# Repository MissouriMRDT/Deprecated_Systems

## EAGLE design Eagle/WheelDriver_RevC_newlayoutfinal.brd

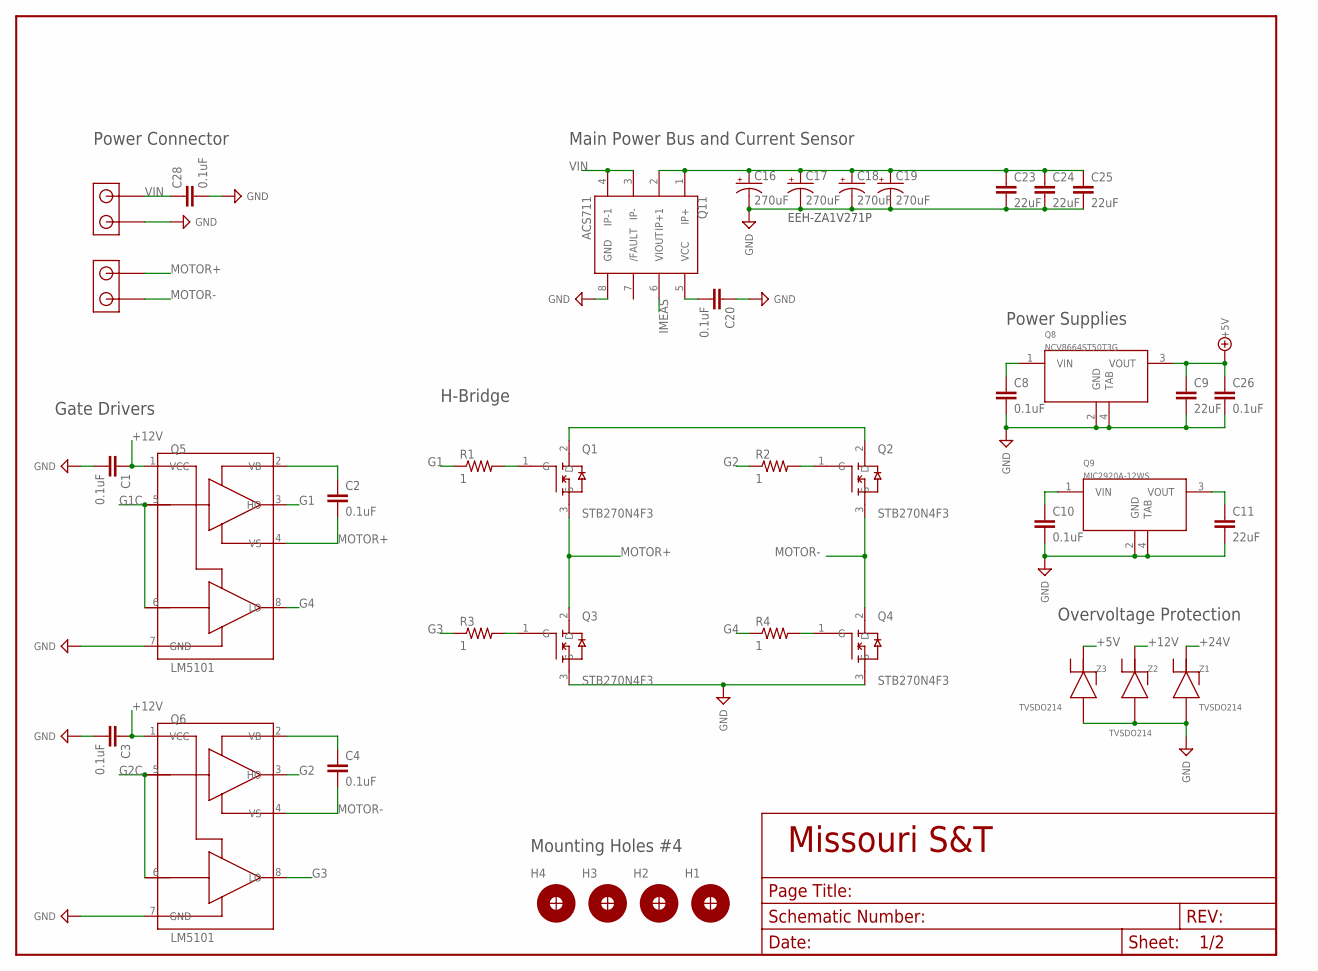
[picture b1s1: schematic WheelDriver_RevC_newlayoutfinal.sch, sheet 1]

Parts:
C1: 0.1uF; C_0805
C2, C3, C4, C8, C10, C20, C26, C28: 0.1uF; C_1206
C9, C11, C23, C24, C25: 22uF; C_1206
C16, C17, C18, C19: 270uF; C_10MMSM
H1, H2, H3, H4: H_MNTHOLE_#4
J4, J5: J_1546074-2; THERM_BLOCK_2
Q1, Q2, Q3, Q4: STB270N4F3; TO-263
Q5, Q6: LM5101; SOIC8
Q8: NCV8664ST50T3G; SOT-223
Q9: MIC2920A-12WS; SOT-223
Q11: ACS711; SOIC8
R1, R2: 1; R_0805
R3, R4: 1; R_1206
Z1, Z2, Z3: TVSDO214; DO-214AC

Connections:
+5V: C9.1, C26.1, Q8.3 (VOUT), Z3.C; also elsewhere on the board
+12V: C1.1, C3.1, C11.1, Q5.1 (VCC), Q6.1 (VCC), Q9.3 (VOUT), Z2.C
+24V: C10.1, C16.+, C17.+, C18.+, C19.+, C23.1, C24.1, C25.1, Q1.2 (D), Q2.2 (D), Q9.1 (VIN), Q11.1 (IP+), Q11.2 (IP+1), Z1.C; also elsewhere on the board
G1: Q5.3 (HO), R1.1
G1C: Q5.5 (HI), Q5.6 (LI); also elsewhere on the board
G2: Q6.3 (HO), R2.1
G2C: Q6.5 (HI), Q6.6 (LI); also elsewhere on the board
G3: Q6.8 (LO), R3.1
G4: Q5.8 (LO), R4.1
GND: C1.2, C3.2, C8.2, C9.2, C10.2, C11.2, C16.-, C17.-, C18.-, C19.-, C20.1, C23.2, C24.2, C25.2, C26.2, C28.2, J4.P$1, Q3.3 (S), Q4.3 (S), Q5.7 (GND), Q6.7 (GND), Q8.2 (GND), Q8.4 (TAB), Q9.2 (GND), Q9.4 (TAB), Q11.8 (GND), Z1.A, Z2.A, Z3.A; also elsewhere on the board
IMEAS: Q11.6 (VIOUT); also elsewhere on the board
MOTOR+: C2.2, J5.P$2, Q1.3 (S), Q3.2 (D), Q5.4 (VS)
MOTOR-: C4.2, J5.P$1, Q2.3 (S), Q4.2 (D), Q6.4 (VS)
unnamed: Q1.1 (G), R1.2
unnamed: Q3.1 (G), R3.2
unnamed: Q2.1 (G), R2.2
unnamed: Q4.1 (G), R4.2
unnamed: C2.1, Q5.2 (VB)
unnamed: C4.1, Q6.2 (VB)
unnamed: C20.2, Q11.5 (VCC)
VIN: C8.1, C28.1, J4.P$2, Q8.1 (VIN), Q11.3 (IP-), Q11.4 (IP-1)

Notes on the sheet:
EEH-ZA1V271P
Power Connector
Gate Drivers
H-Bridge
Overvoltage Protection
Mounting Holes #4
Power Supplies
Main Power Bus and Current Sensor

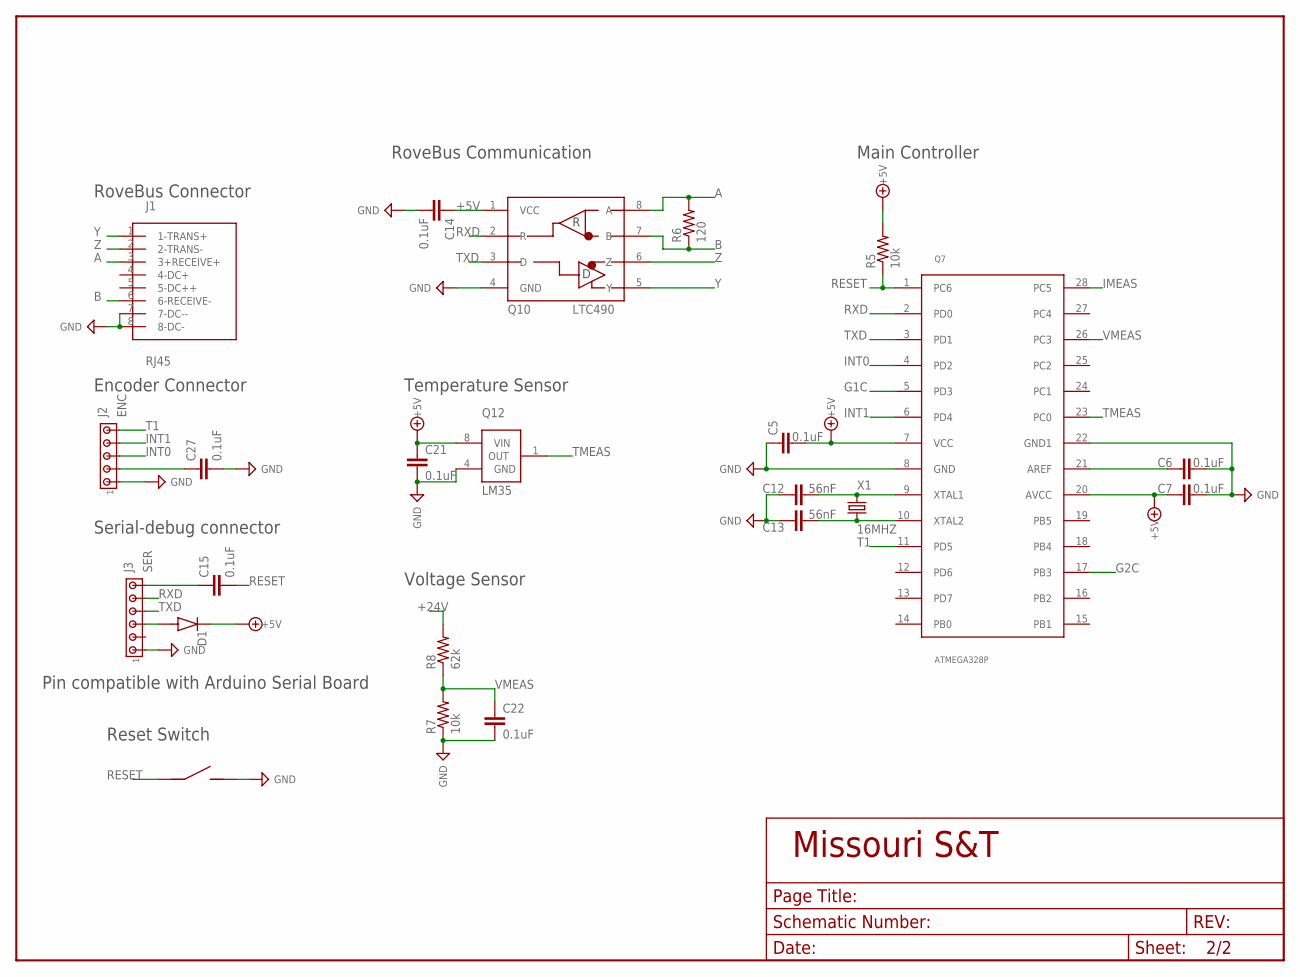
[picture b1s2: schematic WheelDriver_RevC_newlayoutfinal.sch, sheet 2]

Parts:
C5, C14, C27: 0.1uF; C_1206
C6, C7, C15, C21, C22: 0.1uF; C_0805
C12, C13: 56nF; C_1206
D1: D_DIODEDO214AC; DO-214AC
J1: RJ45; RJ45-CAT5E
J2: ENC; J_MTA100_5P
J3: SER; J_MTA100_6P
J6: J_MC32857; J_TOGGLE
Q7: ATMEGA328P; DIP28
Q10: LTC490; SOIC8
Q12: LM35; SOIC8
R5, R7: 10k; R_0805
R6: 120; R_0805
R8: 62k; R_0805
X1: 16MHZ; HC-49

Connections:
+5V: C5.2, C7.1, C14.1, C21.1, C27.1, D1.C, J2.2, Q7.7 (VCC), Q7.20 (AVCC), Q10.1 (VCC), Q12.8 (VIN), R5.2; also elsewhere on the board
+24V: R8.2; also elsewhere on the board
A: J1.3 (3+RECEIVE+), Q10.8 (A), R6.2
B: J1.6 (6-RECEIVE-), Q10.7 (B), R6.1
EXTRESET: C15.1, J3.6
G1C: Q7.5 (PD3); also elsewhere on the board
G2C: Q7.17 (PB3); also elsewhere on the board
GND: C5.1, C6.2, C7.2, C12.1, C13.1, C14.2, C21.2, C22.2, C27.2, J1.7 (7-DC--), J1.8 (8-DC-), J2.1, J3.1, J6.P$2 (2), Q7.8 (GND), Q7.22 (GND1), Q10.4 (GND), Q12.4 (GND), R7.1; also elsewhere on the board
IMEAS: Q7.28 (PC5); also elsewhere on the board
INT0: J2.3, Q7.4 (PD2)
INT1: J2.4, Q7.6 (PD4)
unnamed: C12.2, Q7.9 (XTAL1), X1.P$1 (1)
unnamed: C6.1, Q7.21 (AREF)
unnamed: D1.A, J3.3
unnamed: C13.2, Q7.10 (XTAL2), X1.P$2 (2)
RESET: C15.2, J6.P$1 (1), Q7.1 (PC6), R5.1
RXD: J3.5, Q7.2 (PD0), Q10.2 (R)
T1: J2.5, Q7.11 (PD5)
TMEAS: Q7.23 (PC0), Q12.1 (OUT)
TXD: J3.4, Q7.3 (PD1), Q10.3 (D)
VMEAS: C22.1, Q7.26 (PC3), R7.2, R8.1
Y: J1.1 (1-TRANS+), Q10.5 (Y)
Z: J1.2 (2-TRANS-), Q10.6 (Z)

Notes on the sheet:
RoveBus Connector
Encoder Connector
Serial-debug connector
Pin compatible with Arduino Serial Board
Reset Switch
RoveBus Communication
Temperature Sensor
Voltage Sensor
Main Controller

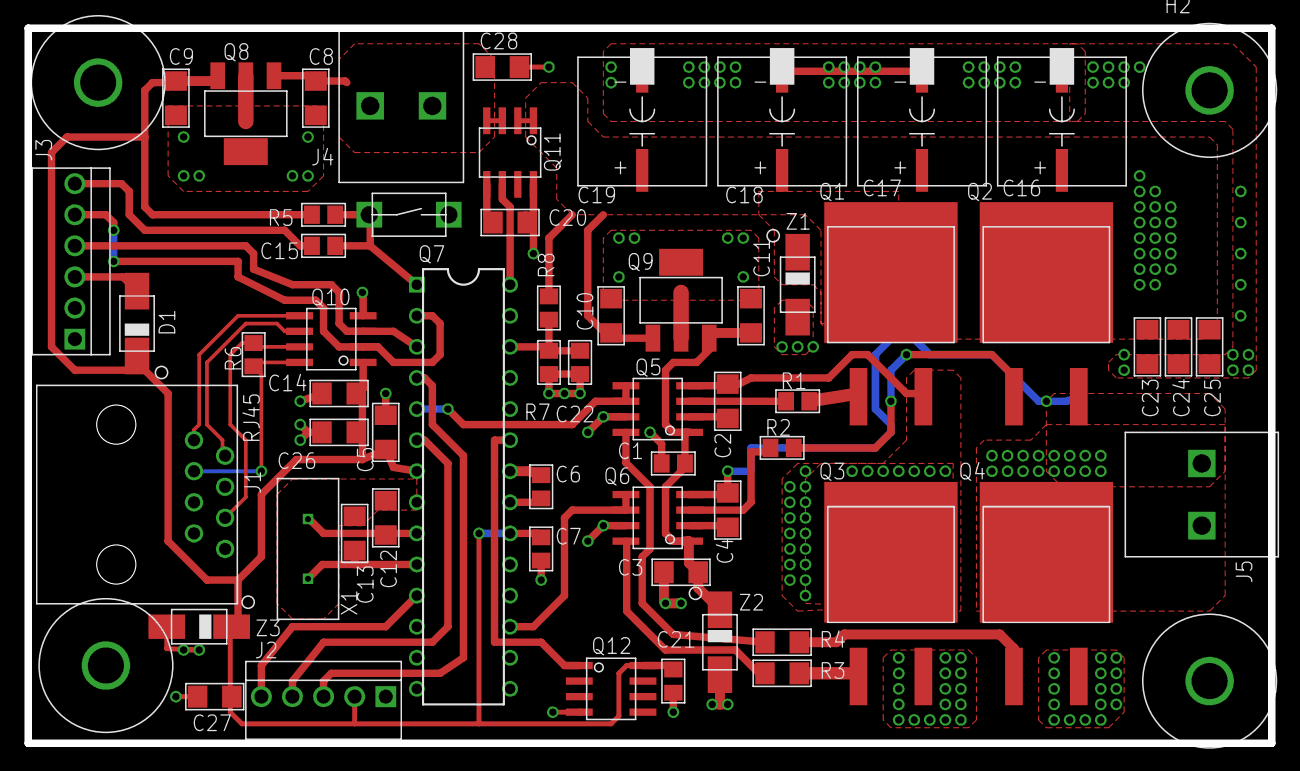
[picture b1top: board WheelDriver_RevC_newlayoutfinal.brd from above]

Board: 2 copper layers, 101.6 x 58.4 mm, 63 parts (0 on the bottom side), 38 nets.

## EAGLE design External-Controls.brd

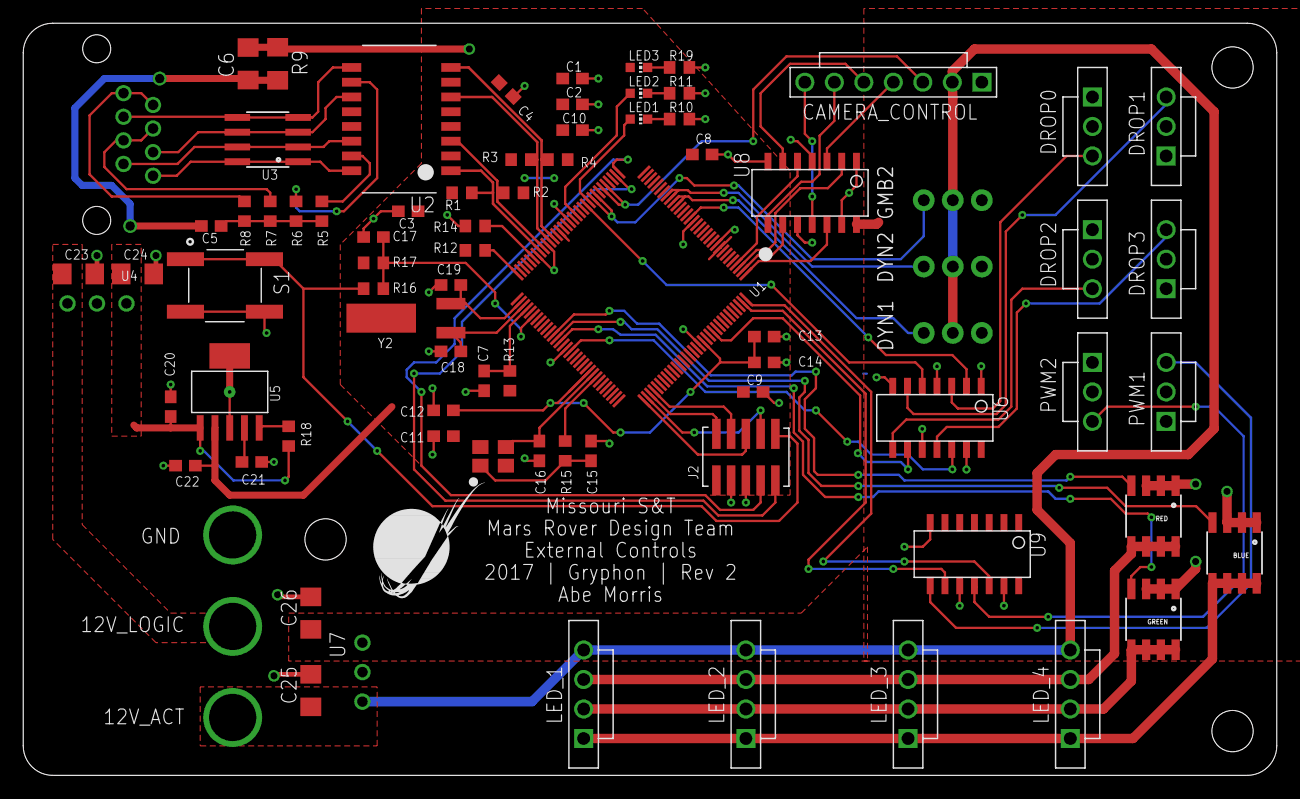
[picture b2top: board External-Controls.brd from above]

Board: 2 copper layers, 108.0 x 64.8 mm, 85 parts (0 on the bottom side), 74 nets.

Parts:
BLUE: IRF7821TRPBF; SOIC8
C1, C2, C3, C4, C7, C8, C9, C10, C11, C12, C17, C20, C21: 0.1uF; C0603
C5: 1000pF; C0603
C6: 4700pF; C1206
C13: 1.0uF; C0603
C14, C22: 2.2uF; C0603
C15, C16, C18, C19: 12pF; C0603
C23, C24, C25, C26: 10uF; C1206
CAMERA_CONTROL: SL07; MOLEX-70543-0006
DROP0, DROP1, DROP2, DROP3: SERVOMOLEX_SL_VERT_TH; MOLEX-70543-0002
DYN1, DYN2: DYNAMIXEL-1X03VERT; MLX-SPOX5267-3PIN
GMB2: DYNAMIXEL-1X03VERT; MLX-SPOX5267-3PIN
GREEN: IRF7821TRPBF; SOIC8
J1: RJ45KEYSTONE-942; KEYSTONE-942
J2: JTAG_ARM_10PIN; CON_2X5_50MIL
J3: APP_2POS_CONFIG12V_HORIZ; APP45_12V_HORIZ_CONFIG
J8: APPPP45_PCB_HORIZ_RIGHT; APP45_PCB_HORIZ_RIGHT
LED1, LED2: GREEN; CHIP-LED0603
LED3: ORANGE; CHIP-LED0603
LED_1, LED_2, LED_3, LED_4: SL04VERT; MOLEX-70543-0003
PWM1, PWM2: SERVOMOLEX_SL_VERT_TH; MOLEX-70543-0002
R1, R3, R4: 49.9; R0603
R2: 49.4; R0603
R5, R6, R7, R8: 75; R0603
R9: 1M; R1206
R10, R11, R19: 330; R0603
R12: 1M; R0603
R13: 51; R0603
R14: 4.87k 1%; R0603
R15: 2k; R0603
R16: 100; R0603
R17: 10k; R0603
R18: 100k; R0603
RED: IRF7821TRPBF; SOIC8
S1: SWITCH_TACTILE; SWITCH_6MM_6MM_TE_CON_SMD
U1: TM4C1294NCPDT; TQFP-128
U2: HX1198FNL
U3: SLVU2.8-4; SOIC8
U4, U7: OKI-78SR-5/1.5-W36HC; OKI-78SR_HORIZ
U5: TPS73733DCQ; SOT-223-6
U6, U8, U9: SN74AHCT125; SOIC14
U$1: MRDT_LOGO
U$2, U$3, U$4: MOUNTING_HOLE#6; #6_SCREW
Y1: NX3225GA; NDK3.2X2.5
Y2: CRYATL_32K_SMD; CRYSTAL_32K_SMD

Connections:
!RESET: J2.P10, R16.2, S1.P$3, S1.P$4
+3V3: C1.1, C2.1, C3.1, C4.1, C8.1, C9.1, C10.1, C11.1, C22.1, J2.P1, LED3.A, R1.1, R2.1, R3.1, R4.1, R12.2, R13.2, R17.1, U1.P$7, U1.P$8, U1.P$9, U1.P$16, U1.P$26, U1.P$28, U1.P$39, U1.P$47, U1.P$51, U1.P$52, U1.P$69, U1.P$79, U1.P$90, U1.P$101, U1.P$113, U1.P$122, U2.P$2, U2.P$7, U5.2
+5V_ACT: C26.1, DROP0.2, DROP1.2, DROP2.2, DROP3.2, PWM1.2, PWM2.2, U6.14, U7.3, U8.14, U9.1, U9.4, U9.14
+5V_LOGIC: C20.1, C24.1, R18.1, U4.3, U5.1
+12V_ACT: C25.1, CAMERA_CONTROL.2, DYN1.VCC, DYN2.VCC, GMB2.VCC, J8.P$1, LED_1.4, LED_2.4, LED_3.4, LED_4.4, U7.1
+12V_LOGIC: C23.1, J3.12V, U4.1
BLUE: BLUE.5, BLUE.6, BLUE.7, BLUE.8, LED_1.1, LED_2.1, LED_3.1, LED_4.1
BLUE_SIG: BLUE.4, U1.P$77
CAM_PWM_0: CAMERA_CONTROL.4, U8.3
CAM_PWM_1: CAMERA_CONTROL.5, U8.6
CAM_PWM_2: CAMERA_CONTROL.6, U8.8
CAM_PWM_3: CAMERA_CONTROL.7, U8.11
CTRL_0: U1.P$3, U8.2
CTRL_1: U1.P$4, U8.5
CTRL_2: U1.P$2, U8.9
CTRL_3: U1.P$1, U8.12
DROPBAY_0: U1.P$18, U6.2
DROPBAY_1: U1.P$43, U6.5
DROPBAY_2: U1.P$118, U6.9
DROPBAY_3: U1.P$81, U6.12
DYN_1: CAMERA_CONTROL.3, U1.P$37, U1.P$38
DYN_2: GMB2.DATA, U1.P$40, U1.P$41
DYN_3: DYN1.DATA, U1.P$22, U1.P$23
DYN_4: DYN2.DATA, U1.P$24, U1.P$25
EN0LED0: LED1.A, U1.P$42
EN0LED1: LED2.A, U1.P$46
EN0RXI_N: R4.2, U1.P$53, U2.P$8
EN0RXI_P: R3.2, U1.P$54, U2.P$6
EN0TXO_N: R2.2, U1.P$56, U2.P$3
EN0TXO_P: R1.2, U1.P$57, U2.P$1
GND: BLUE.1, BLUE.2, BLUE.3, C1.2, C2.2, C3.2, C4.2, C6.2, C7.2, C8.2, C9.2, C10.2, C11.2, C12.2, C13.2, C14.2, C15.2, C16.2, C17.2, C18.2, C19.2, C20.2, C21.2, C22.2, C23.2, C24.2, C25.2, C26.2, CAMERA_CONTROL.1, DROP0.1, DROP1.1, DROP2.1, DROP3.1, DYN1.GND, DYN2.GND, GMB2.GND, GREEN.1, GREEN.2, GREEN.3, J2.P3, J2.P5, J3.GND, PWM1.1, PWM2.1, R9.1, R10.2, R11.2, R14.1, R19.2, RED.1, RED.2, RED.3, S1.P$1, S1.P$2, U1.P$10, U1.P$17, U1.P$48, U1.P$55, U1.P$58, U1.P$80, U1.P$114, U4.2, U5.3, U5.6, U6.1, U6.4, U6.7, U6.10, U6.13, U7.2, U8.1, U8.4, U8.7, U8.10, U8.13, U9.7, U9.10, U9.13
GREEN: GREEN.5, GREEN.6, GREEN.7, GREEN.8, LED_1.2, LED_2.2, LED_3.2, LED_4.2
GREEN_SIG: GREEN.4, U1.P$78
N_$1: R5.2, U2.P$15
N_$3: R6.2, U2.P$10
N_$4: J1.P$7, U2.P$14, U3.2, U3.7
N_$5: J1.P$6, U2.P$11, U3.3, U3.6
N_$6: J1.P$8, U2.P$16, U3.1, U3.8
N_$7: J1.P$3, U2.P$9, U3.4, U3.5
N_$8: LED2.C, R11.1
N_$9: LED1.C, R10.1
N_$10: C7.1, R13.1, U1.P$68
N_$11: J1.P$4, J1.P$5, R7.2
N_$12: R12.1, U1.P$64
N_$13: J1.P$1, J1.P$2, R8.2
N_$14: C5.1, R5.1, R6.1, R7.1, R8.1
N_$15: C5.2, C6.1, R9.2
N_$16: C12.1, C13.1, C14.1, U1.P$87, U1.P$115
N_$17: R15.2, U1.P$89
N_$18: C16.1, U1.P$88, Y1.P$3
N_$19: R14.2, U1.P$59
N_$20: C17.1, R16.1, R17.2, U1.P$70
N_$21: C15.1, R15.1, Y1.P$1
N_$22: C18.1, U1.P$67, Y2.P$2
N_$23: C19.1, U1.P$66, Y2.P$1
N_$25: R18.2, U5.5
N_$26: LED3.C, R19.1
N_$27: C21.1, U5.4
PWM1: U1.P$128, U9.12
PWM2: U1.P$127, U9.9
RED: LED_1.3, LED_2.3, LED_3.3, LED_4.3, RED.5, RED.6, RED.7, RED.8
RED_SIG: RED.4, U1.P$76
RX: J2.P7, U1.P$33
SERVO_0: DROP0.3, U6.3
SERVO_1: DROP1.3, U6.6
SERVO_2: DROP2.3, U6.8
SERVO_3: DROP3.3, U6.11
SERVO_4: PWM2.3, U9.11
SERVO_5: PWM1.3, U9.8
TARGET_TCK/SWCLK: J2.P4, U1.P$100
TARGET_TDI: J2.P8, U1.P$98
TARGET_TDO/SWO: J2.P6, U1.P$97
TARGET_TMS/SWDIO: J2.P2, U1.P$99
TX: J2.P9, U1.P$34

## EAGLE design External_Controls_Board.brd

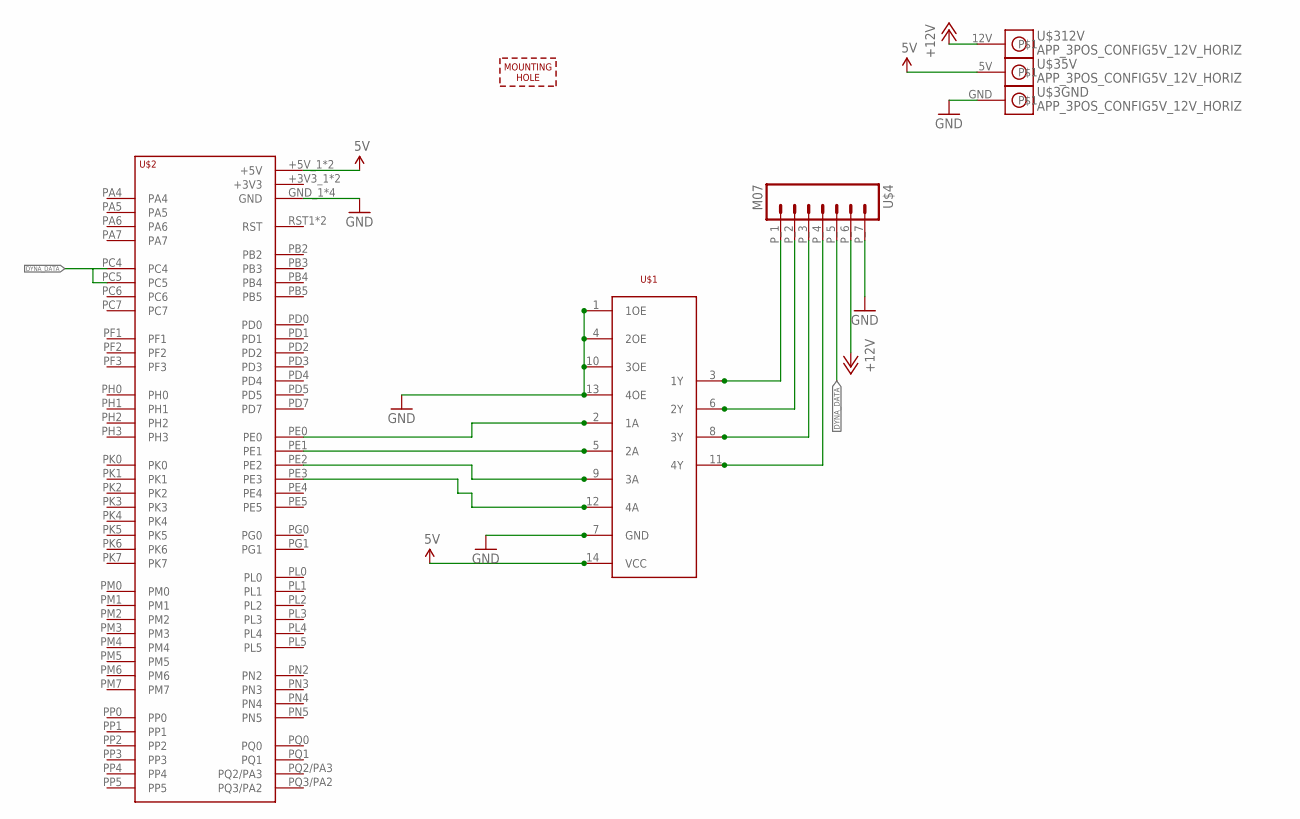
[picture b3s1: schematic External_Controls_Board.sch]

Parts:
U$1: SN74AHCT125; SOIC14
U$2: TIVA-C-CONNECTED
U$3: APP_3POS_CONFIG5V_12V_HORIZ; APP45_5V_12V_HORIZ_CONFIG
U$4: M07; MOLEX_43650-07
U$6: MOUNTING_HOLE#8; #8_SCREW

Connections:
+5V: U$1.14 (VCC), U$2.+5V_1 (+5V), U$2.+5V_2 (+5V), U$3.5V
+12V: U$3.12V, U$4.P_6 (6)
DYNA_DATA: U$2.PC4, U$2.PC5, U$4.P_5 (5)
GND: U$1.1 (1OE), U$1.4 (2OE), U$1.7 (GND), U$1.10 (3OE), U$1.13 (4OE), U$2.GND_1 (GND), U$2.GND_2 (GND), U$2.GND_3 (GND), U$2.GND_4 (GND), U$3.GND, U$4.P_7 (7)
PWM0_3.3: U$1.12 (4A), U$2.PE3
PWM0_5: U$1.11 (4Y), U$4.P_4 (4)
PWM1_3.3: U$1.9 (3A), U$2.PE2
PWM1_5: U$1.8 (3Y), U$4.P_3 (3)
PWM2_3.3: U$1.5 (2A), U$2.PE1
PWM2_5: U$1.6 (2Y), U$4.P_2 (2)
PWM3_3.3: U$1.2 (1A), U$2.PE0
PWM3_5: U$1.3 (1Y), U$4.P_1 (1)

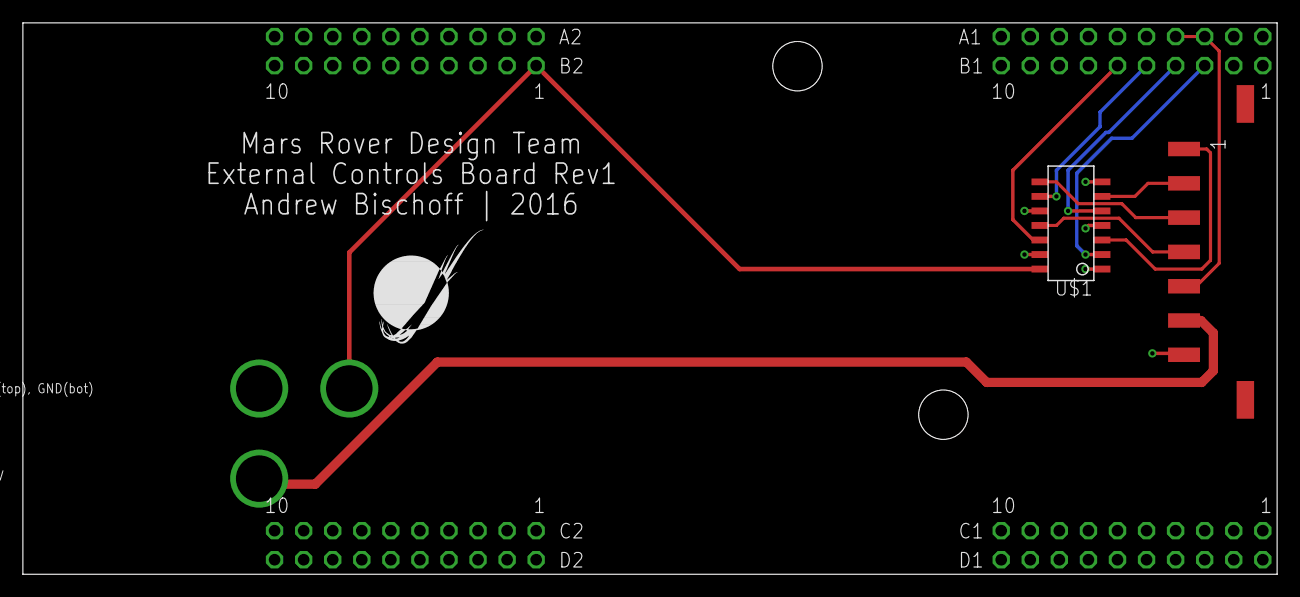
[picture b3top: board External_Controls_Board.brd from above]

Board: 2 copper layers, 109.6 x 48.2 mm, 7 parts (0 on the bottom side), 12 nets.

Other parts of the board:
U$5: MOUNTING_HOLE#8; #8_SCREW
U$7: MRDT_LOGO

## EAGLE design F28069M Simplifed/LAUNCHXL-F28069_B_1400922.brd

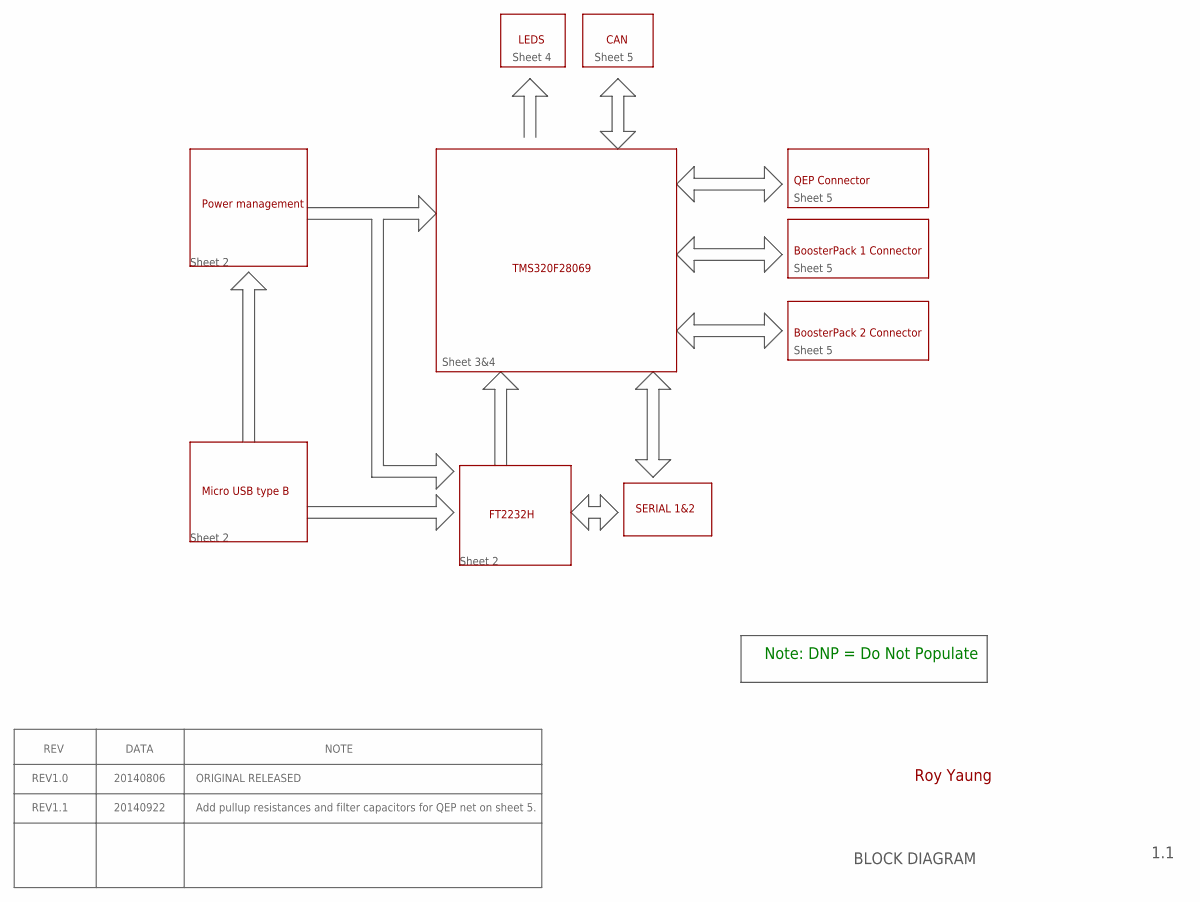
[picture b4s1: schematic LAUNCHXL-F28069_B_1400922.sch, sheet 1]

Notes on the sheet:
1.1
BLOCK DIAGRAM
Power management
Micro USB type B
FT2232H
TMS320F28069
BoosterPack 1 Connector
LEDS
CAN
SERIAL 1&2
Sheet 2
Sheet 3&4
BoosterPack 2 Connector
QEP Connector
Note: DNP = Do Not Populate
Roy Yaung
Sheet 5
Sheet 4
REV
DATA
NOTE
REV1.0
REV1.1
20140806
20140922
ORIGINAL RELEASED
Add pullup resistances and filter capacitors for QEP net on sheet 5.

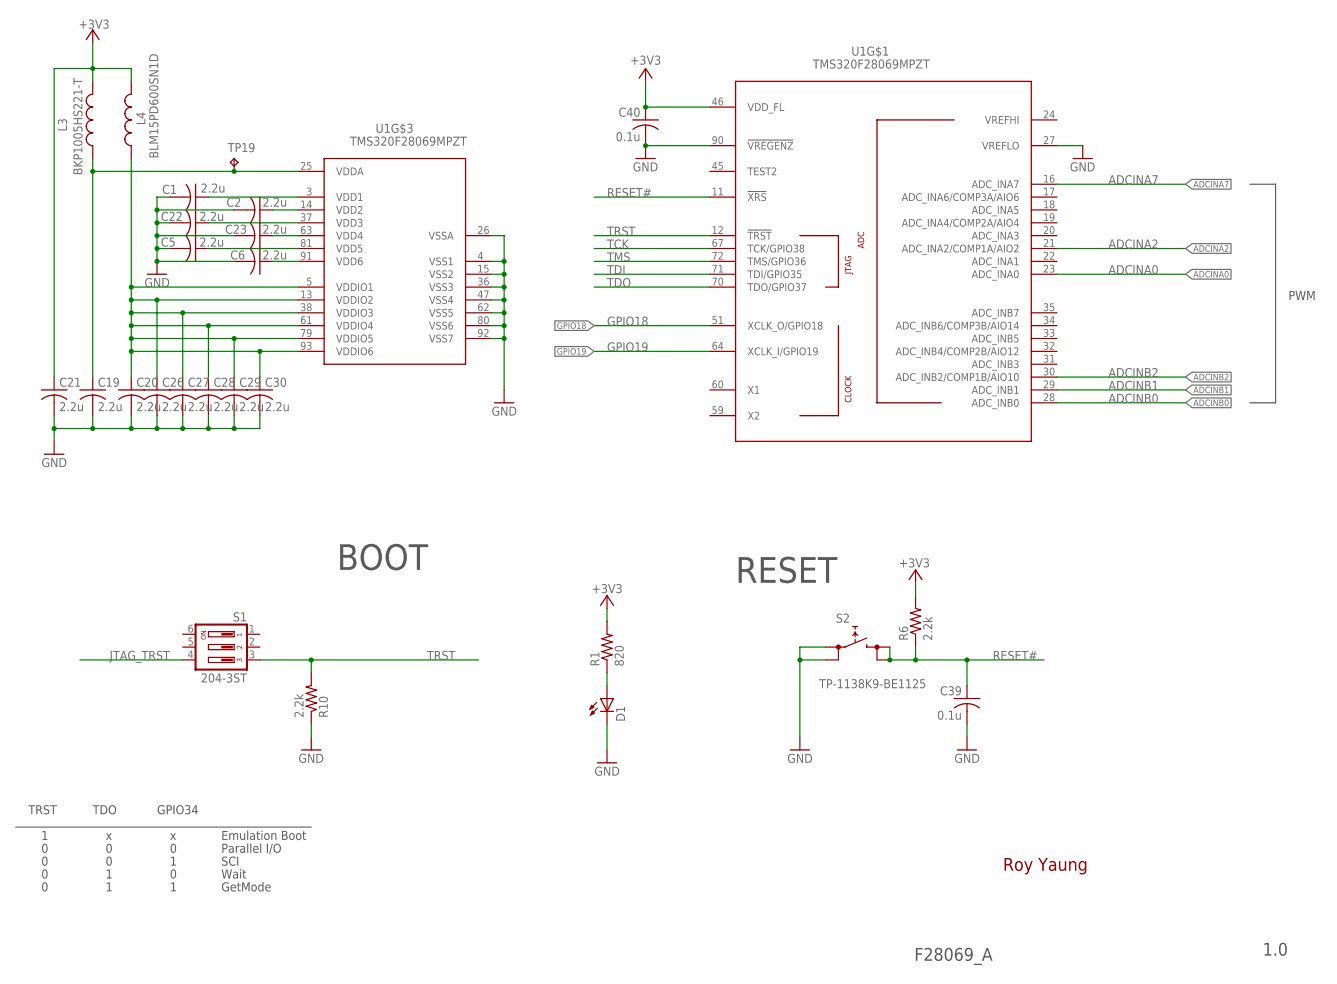
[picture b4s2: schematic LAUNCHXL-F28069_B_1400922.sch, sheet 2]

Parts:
C1, C2, C5, C6, C19, C20, C21, C22, C23, C26, C27, C28, C29, C30: 2.2u; C0402
C39, C40: 0.1u; C0402
D1: LEDCHIP-LED0603; CHIP-LED0603
L3: BKP1005HS221-T; R0402
L4: BLM15PD600SN1D; R0402
R1: 820; R0402
R6, R10: 2.2k; R0402
S1: 204-3ST; CTS-219-03
S2: TP-1138K9-BE1125; FSMJSMA
TP19: TESTPAD_TPB1,27; TESTPAD_B1,27
U1: TMS320F28069MPZT; PQFP100

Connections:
+3V3: C21.1, C40.1, L3.2, L4.2, R1.2, R6.2, U1.46 (VDD_FL); also elsewhere on the board
ADCINA0: U1.23 (ADC_INA0); also elsewhere on the board
ADCINA2: U1.21 (ADC_INA2/COMP1A/AIO2); also elsewhere on the board
ADCINA7: U1.16 (ADC_INA7); also elsewhere on the board
ADCINB0: U1.28 (ADC_INB0); also elsewhere on the board
ADCINB1: U1.29 (ADC_INB1); also elsewhere on the board
ADCINB2: U1.30 (ADC_INB2/COMP1B/AIO10); also elsewhere on the board
GND: C1.2, C2.2, C5.2, C6.2, C19.2, C20.2, C21.2, C22.2, C23.2, C26.2, C27.2, C28.2, C29.2, C30.2, C39.2, C40.2, D1.C, R10.1, S2.P$1 (0), S2.P$2 (0), U1.4 (VSS1), U1.15 (VSS2), U1.26 (VSSA), U1.27 (VREFLO), U1.36 (VSS3), U1.47 (VSS4), U1.62 (VSS5), U1.80 (VSS6), U1.90 (!VREGENZ), U1.92 (VSS7); also elsewhere on the board
GPIO18: U1.51 (XCLK_O/GPIO18); also elsewhere on the board
GPIO19: U1.64 (XCLK_I/GPIO19); also elsewhere on the board
JTAG_TRST: S1.4; also elsewhere on the board
unnamed: D1.A, R1.1
unnamed: C1.1, U1.3 (VDD1)
unnamed: C2.1, U1.14 (VDD2)
unnamed: C22.1, U1.37 (VDD3)
unnamed: C23.1, U1.63 (VDD4)
unnamed: C5.1, U1.81 (VDD5)
unnamed: C6.1, U1.91 (VDD6)
RESET#: C39.1, R6.1, S2.P$3 (1), S2.P$4 (1), U1.11 (!XRS); also elsewhere on the board
TCK: U1.67 (TCK/GPIO38); also elsewhere on the board
TDI: U1.71 (TDI/GPIO35); also elsewhere on the board
TDO: U1.70 (TDO/GPIO37); also elsewhere on the board
TMS: U1.72 (TMS/GPIO36); also elsewhere on the board
TRST: R10.2, S1.3, U1.12 (!TRST)
VDDA: C19.1, L3.1, TP19.TP, U1.25 (VDDA)
VDDIO: C20.1, C26.1, C27.1, C28.1, C29.1, C30.1, L4.1, U1.5 (VDDIO1), U1.13 (VDDIO2), U1.38 (VDDIO3), U1.61 (VDDIO4), U1.79 (VDDIO5), U1.93 (VDDIO6)

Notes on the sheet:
1.0
F28069_A
PWM
TDO
GPIO34
TRST
Emulation Boot
Parallel I/O
SCI
Wait
GetMode
RESET
BOOT
Roy Yaung

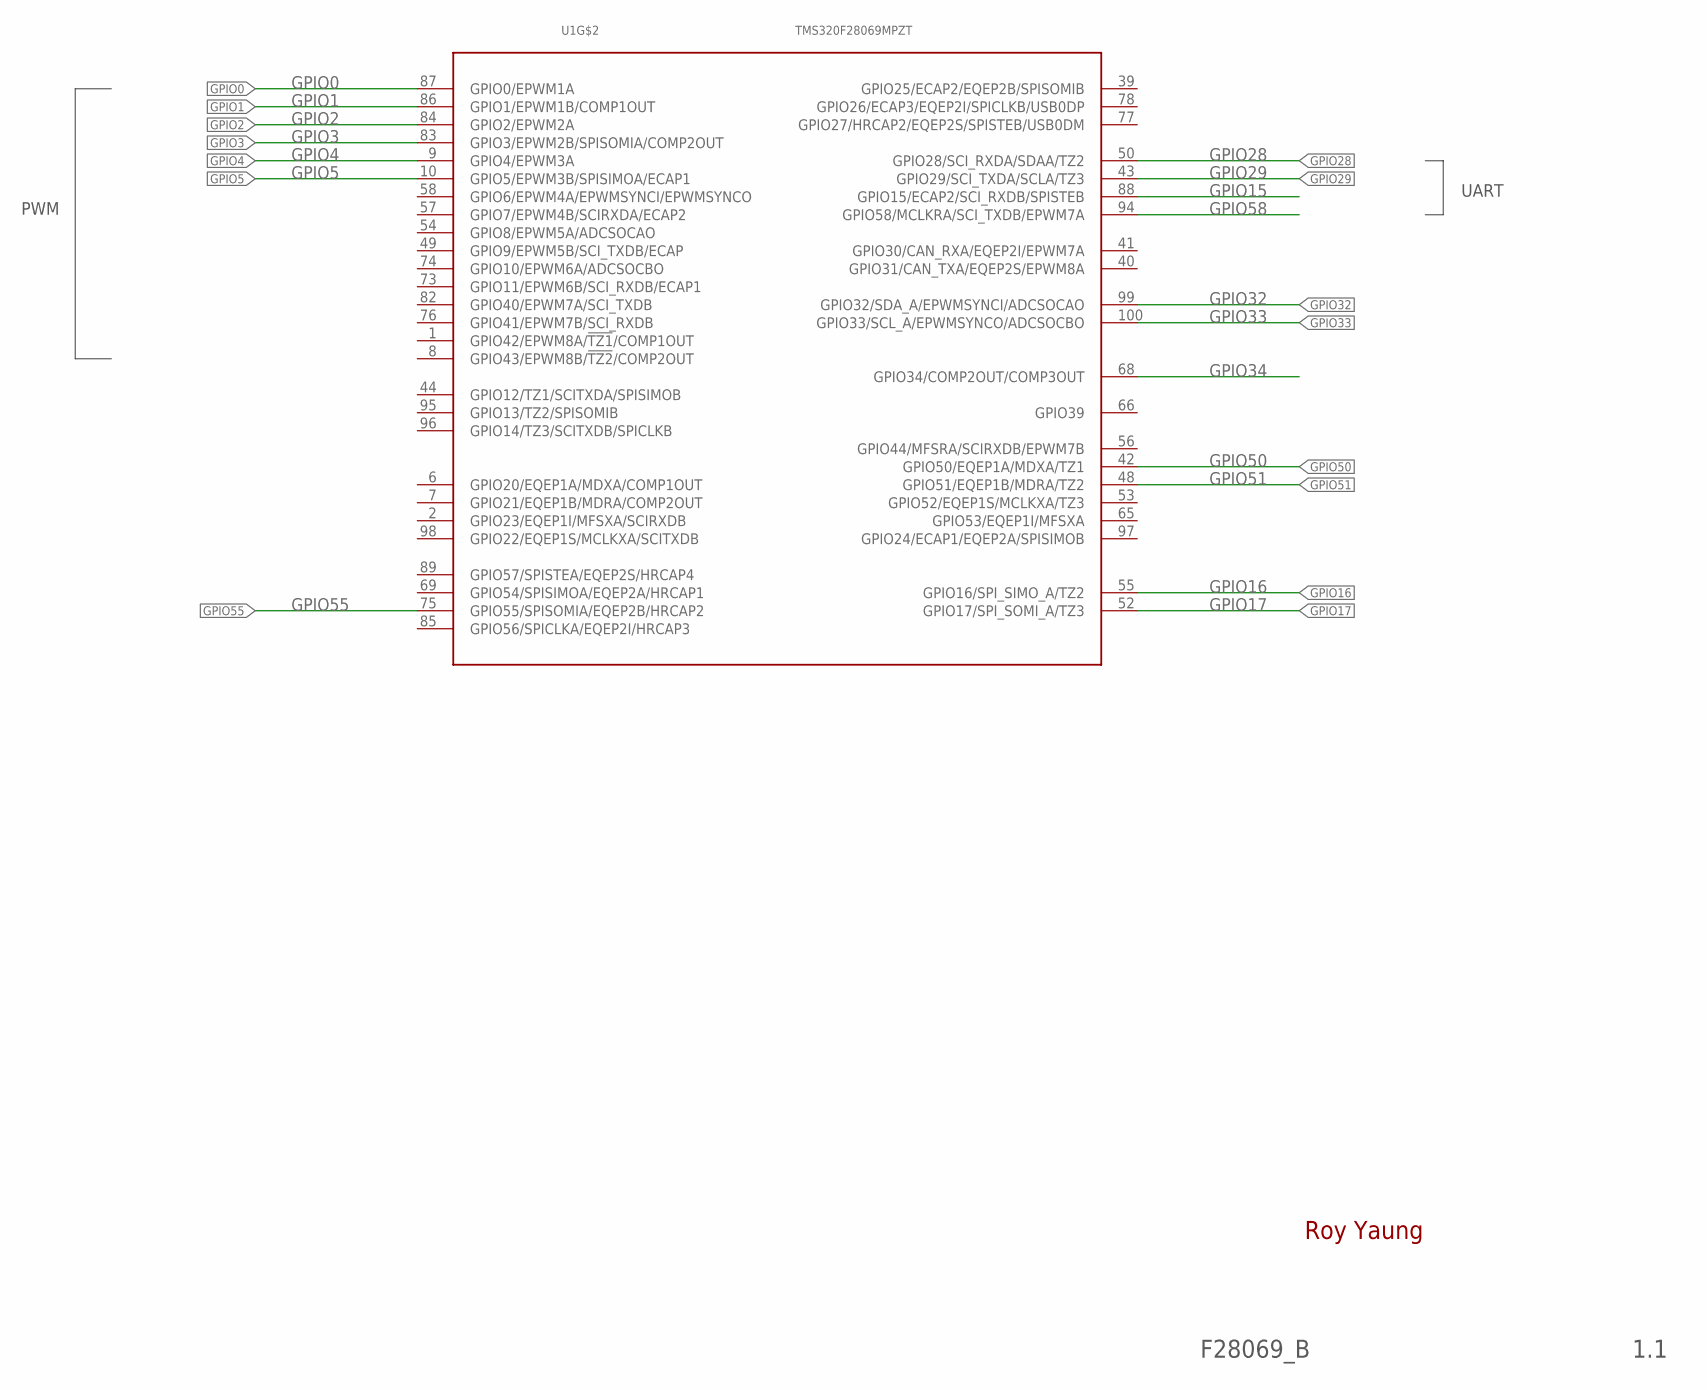
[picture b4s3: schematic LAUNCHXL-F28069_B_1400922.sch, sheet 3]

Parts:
U1: TMS320F28069MPZT; PQFP100

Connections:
GPIO0: U1.87 (GPIO0/EPWM1A); also elsewhere on the board
GPIO1: U1.86 (GPIO1/EPWM1B/COMP1OUT); also elsewhere on the board
GPIO2: U1.84 (GPIO2/EPWM2A); also elsewhere on the board
GPIO3: U1.83 (GPIO3/EPWM2B/SPISOMIA/COMP2OUT); also elsewhere on the board
GPIO4: U1.9 (GPIO4/EPWM3A); also elsewhere on the board
GPIO5: U1.10 (GPIO5/EPWM3B/SPISIMOA/ECAP1); also elsewhere on the board
GPIO15: U1.88 (GPIO15/ECAP2/SCI_RXDB/SPISTEB)
GPIO16: U1.55 (GPIO16/SPI_SIMO_A/TZ2); also elsewhere on the board
GPIO17: U1.52 (GPIO17/SPI_SOMI_A/TZ3); also elsewhere on the board
GPIO28: U1.50 (GPIO28/SCI_RXDA/SDAA/TZ2)
GPIO29: U1.43 (GPIO29/SCI_TXDA/SCLA/TZ3)
GPIO32: U1.99 (GPIO32/SDA_A/EPWMSYNCI/ADCSOCAO); also elsewhere on the board
GPIO33: U1.100 (GPIO33/SCL_A/EPWMSYNCO/ADCSOCBO); also elsewhere on the board
GPIO34: U1.68 (GPIO34/COMP2OUT/COMP3OUT)
GPIO50: U1.42 (GPIO50/EQEP1A/MDXA/TZ1); also elsewhere on the board
GPIO51: U1.48 (GPIO51/EQEP1B/MDRA/TZ2); also elsewhere on the board
GPIO55: U1.75 (GPIO55/SPISOMIA/EQEP2B/HRCAP2); also elsewhere on the board
GPIO58: U1.94 (GPIO58/MCLKRA/SCI_TXDB/EPWM7A)

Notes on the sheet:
1.1
F28069_B
PWM
UART
Roy Yaung

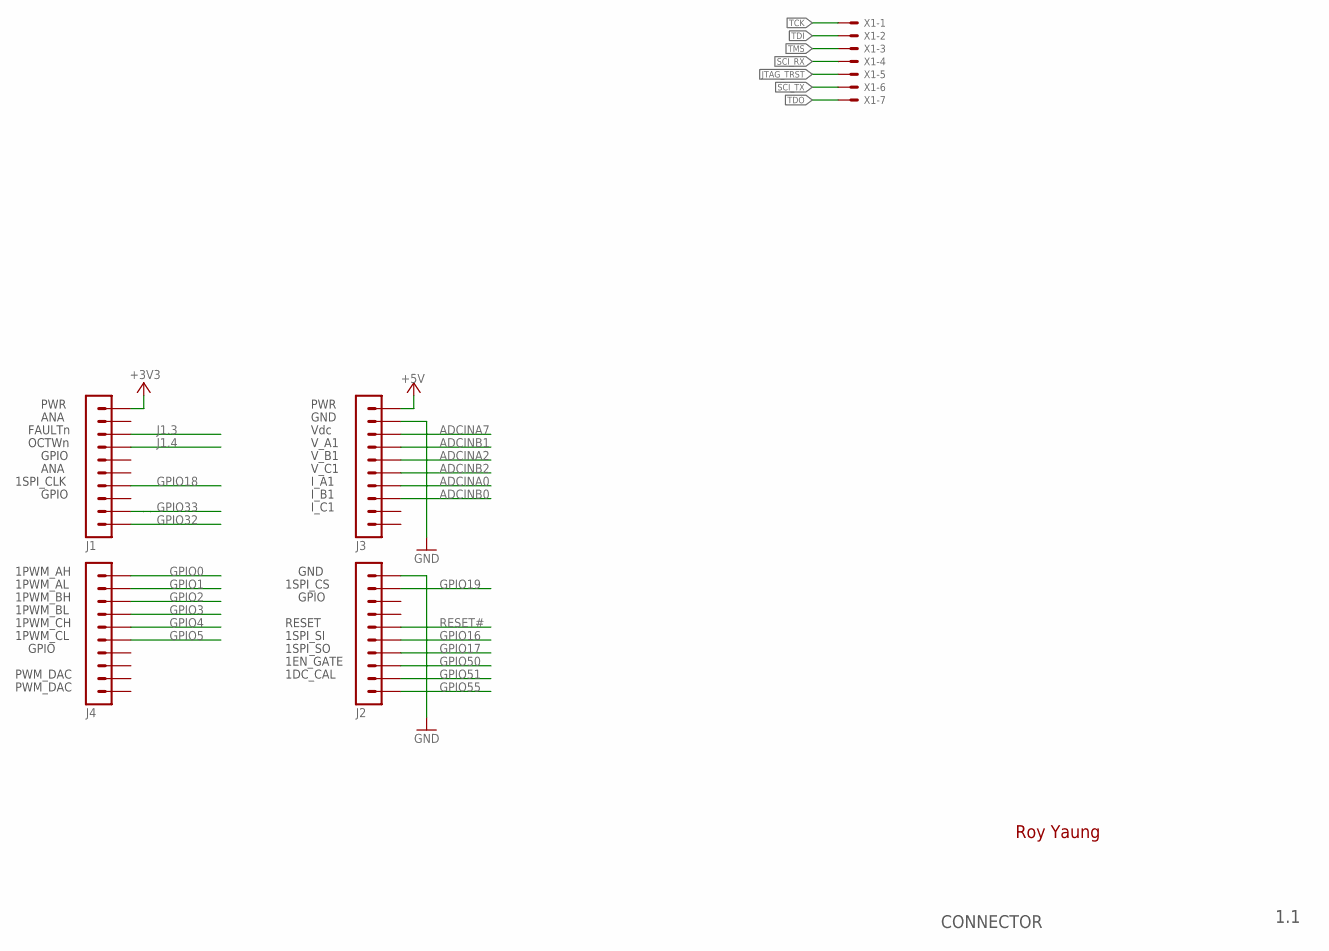
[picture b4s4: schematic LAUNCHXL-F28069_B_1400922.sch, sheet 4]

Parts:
J1, J2, J3, J4: MA10-1
X1: KK-156-7

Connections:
+3V3: J1.1; also elsewhere on the board
+5V: J3.1
ADCINA0: J3.7; also elsewhere on the board
ADCINA2: J3.5; also elsewhere on the board
ADCINA7: J3.3; also elsewhere on the board
ADCINB0: J3.8; also elsewhere on the board
ADCINB1: J3.4; also elsewhere on the board
ADCINB2: J3.6; also elsewhere on the board
GND: J2.1, J3.2; also elsewhere on the board
GPIO0: J4.1; also elsewhere on the board
GPIO1: J4.2; also elsewhere on the board
GPIO2: J4.3; also elsewhere on the board
GPIO3: J4.4; also elsewhere on the board
GPIO4: J4.5; also elsewhere on the board
GPIO5: J4.6; also elsewhere on the board
GPIO16: J2.6; also elsewhere on the board
GPIO17: J2.7; also elsewhere on the board
GPIO18: J1.7; also elsewhere on the board
GPIO19: J2.2; also elsewhere on the board
GPIO32: J1.10; also elsewhere on the board
GPIO33: J1.9; also elsewhere on the board
GPIO50: J2.8; also elsewhere on the board
GPIO51: J2.9; also elsewhere on the board
GPIO55: J2.10; also elsewhere on the board
J1.3: J1.3
J1.4: J1.4
JTAG_TRST: X1.5; also elsewhere on the board
RESET#: J2.5; also elsewhere on the board
SCI_RX: X1.4
SCI_TX: X1.6
TCK: X1.1; also elsewhere on the board
TDI: X1.2; also elsewhere on the board
TDO: X1.7; also elsewhere on the board
TMS: X1.3; also elsewhere on the board

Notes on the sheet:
1.1
CONNECTOR
Vdc
V_A1
V_B1
V_C1
I_A1
I_B1
I_C1
PWR
ANA
FAULTn
OCTWn
GPIO
1SPI_CLK
1PWM_AH
1PWM_AL
1PWM_BH
1PWM_BL
1PWM_CH
1PWM_CL
GND
1SPI_CS
RESET
1SPI_SI
1SPI_SO
1EN_GATE
1DC_CAL
PWM_DAC
Roy Yaung

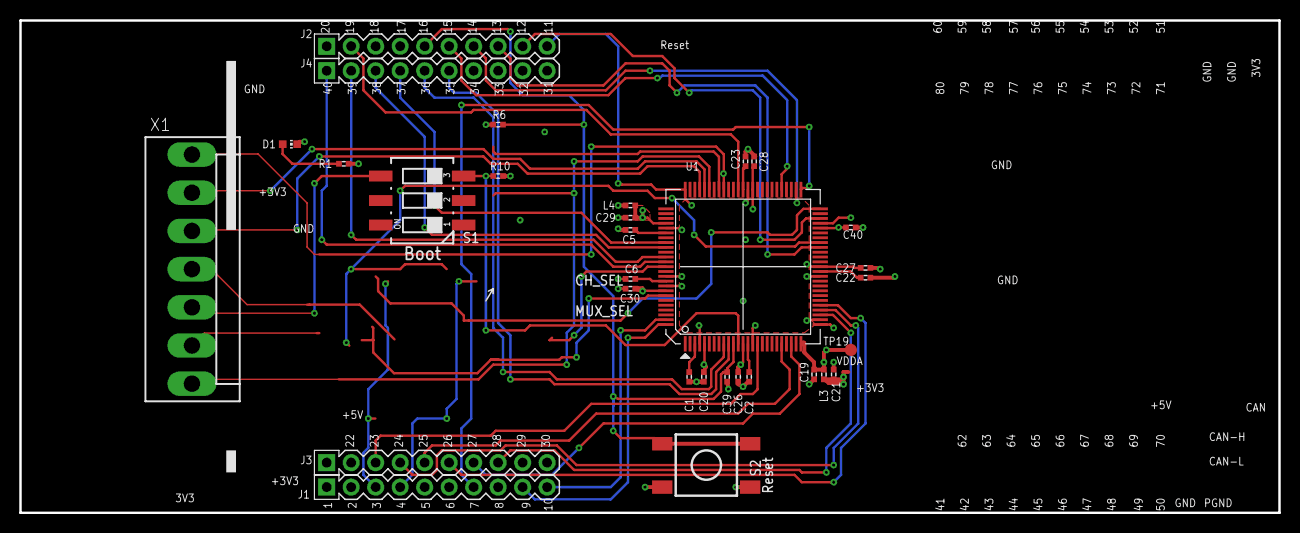
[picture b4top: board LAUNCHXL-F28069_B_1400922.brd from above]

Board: 2 copper layers, 130.6 x 51.1 mm, 32 parts (0 on the bottom side), 39 nets.

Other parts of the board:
E$3: F28069M_BACKSILK_2

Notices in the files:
parts and their libraries:
SparkFun-Aesthetics: Licensing: CC v3.0 Share-Alike You are welcome to use this library for commercial purposes.
SparkFun-Capacitors: Licensing: Creative Commons ShareAlike 4.0 International - https://creativecommons.org/licenses/by-sa/4.0
